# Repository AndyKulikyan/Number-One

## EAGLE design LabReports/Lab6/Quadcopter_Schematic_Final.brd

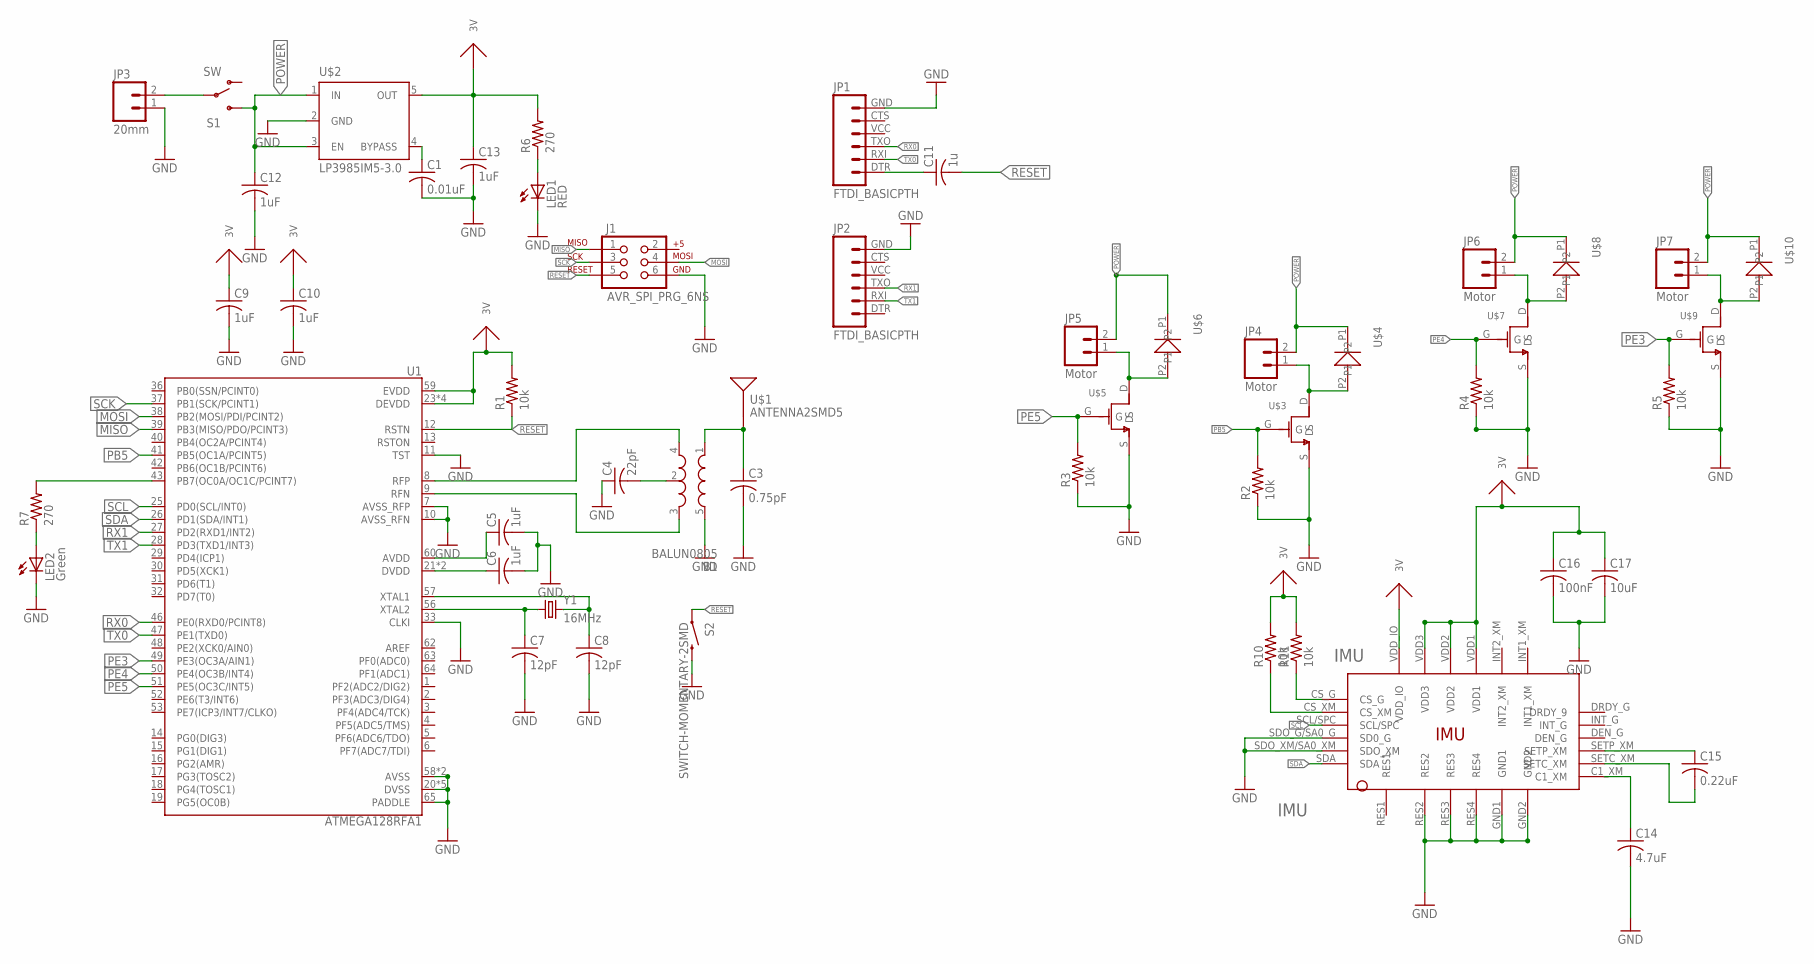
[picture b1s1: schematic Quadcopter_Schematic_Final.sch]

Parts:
B1: BALUN0805; BALUN
C1: 0.01uF; C0805
C3: 0.75pF; C0805
C4: 22pF; C0805
C5, C6, C9, C10, C12, C13: 1uF; C0805
C7, C8: 12pF; C0805
C11: 1u; C0805
C14: 4.7uF; C0805
C15: 0.22uF; C0805
C16: 100nF; C0805
C17: 10uF; C0805
IMU: IMU; LSM9DS0
J1: AVR_SPI_PRG_6NS; 2X3-NS
JP1, JP2: FTDI_BASICPTH; FTDI_BASIC
JP3: 20mm; 1X02
JP4, JP5, JP6, JP7: Motor; 1X02
LED1: RED; CHIP-LED0805
LED2: Green; CHIP-LED0805
R1, R2, R3, R4, R5, R10, R11: 10k; R0805
R6, R7: 270; R0805
S1: SW; SWITCH-SPDT
S2: SWITCH-MOMENTARY-2SMD; TACTILE_SWITCH_SMD
U1: ATMEGA128RFA1; QFN-64
U$1: ANTENNA2SMD5; ANTENNA-CHIP5
U$2: LP3985IM5-3.0; SOT23-DBV
U$3, U$5, U$7, U$9: NMOS; SI2302DS_MOSFET
U$4, U$6, U$8, U$10: Diode; BAS16WS_DIODE
Y1: 16MHz; CRYSTAL-SMD-5X3

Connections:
3V: C9.1, C10.1, C13.1, C16.1, C17.1, IMU.VDD1, IMU.VDD2, IMU.VDD3, IMU.VDD_IO, R1.2, R6.2, R10.2, R11.2, U1.23 (DEVDD), U1.34 (DEVDD), U1.44 (DEVDD), U1.54 (DEVDD), U1.59 (EVDD), U$2.5 (OUT)
FTDI: C11.1, JP1.DTR (1)
GND: B1.5 (GND), C1.2, C3.2, C4.1, C5.2, C6.2, C7.2, C8.2, C9.2, C10.2, C12.2, C13.2, C14.2, C16.2, C17.2, IMU.GND1, IMU.GND2, IMU.RES2, IMU.RES3, IMU.RES4, IMU.SDO_G/SA0_G (SD0_G), IMU.SDO_XM/SA0_XM (SDO_XM), J1.6, JP1.GND (6), JP2.GND (6), JP3.1, LED1.C, LED2.C, R2.1, R3.1, R4.1, R5.1, S2.3 (2), U1.7 (AVSS_RFP), U1.10 (AVSS_RFN), U1.11 (TST), U1.20 (DVSS), U1.24 (DVSS), U1.33 (CLKI), U1.35 (DVSS), U1.45 (DVSS), U1.55 (DVSS), U1.58 (AVSS), U1.61 (AVSS), U1.65 (PADDLE), U$2.2 (GND), U$3.S, U$5.S, U$7.S, U$9.S
MISO: J1.1, U1.39 (PB3(MISO/PDO/PCINT3))
MOSI: J1.4, U1.38 (PB2(MOSI/PDI/PCINT2))
unnamed: B1.4 (OUT1), U1.8 (RFP)
unnamed: JP5.1, U$5.D, U$6.P2
unnamed: JP3.2, S1.2
unnamed: C5.1, U1.60 (AVDD)
unnamed: C6.1, U1.21 (DVDD), U1.22 (DVDD)
unnamed: B1.2 (GND), C4.2
unnamed: B1.3 (OUT2), U1.9 (RFN)
unnamed: C8.1, U1.57 (XTAL1), Y1.3 (2)
unnamed: B1.1 (IN), C3.1, U$1.FEED
unnamed: LED1.A, R6.1
unnamed: LED2.A, R7.1
unnamed: C7.1, U1.56 (XTAL2), Y1.1
unnamed: C1.1, U$2.4 (BYPASS)
unnamed: IMU.CS_G, R11.1
unnamed: IMU.CS_XM, R10.1
unnamed: JP4.1, U$3.D, U$4.P2
unnamed: C14.1, IMU.C1_XM
unnamed: C15.2, IMU.SETC_XM
unnamed: C15.1, IMU.SETP_XM
unnamed: JP6.1, U$7.D, U$8.P2
unnamed: JP7.1, U$9.D, U$10.P2
PB5: R2.2, U1.41 (PB5(OC1A/PCINT5)), U$3.G
PB7: R7.2, U1.43 (PB7(OC0A/OC1C/PCINT7))
PE3: R5.2, U1.49 (PE3(OC3A/AIN1)), U$9.G
PE4: R4.2, U1.50 (PE4(OC3B/INT4)), U$7.G
PE5: R3.2, U1.51 (PE5(OC3C/INT5)), U$5.G
POWER: C12.1, JP4.2, JP5.2, JP6.2, JP7.2, S1.3 (S), U$2.1 (IN), U$2.3 (EN), U$4.P1, U$6.P1, U$8.P1, U$10.P1
RESET: C11.2, J1.5, R1.1, S2.1, U1.12 (RSTN)
RX0: JP1.TXO (3), U1.46 (PE0(RXD0/PCINT8))
RX1: JP2.TXO (3), U1.27 (PD2(RXD1/INT2))
SCK: J1.3, U1.37 (PB1(SCK/PCINT1))
SCL: IMU.SCL/SPC, U1.25 (PD0(SCL/INT0))
SDA: IMU.SDA, U1.26 (PD1(SDA/INT1))
TX0: JP1.RXI (2), U1.47 (PE1(TXD0))
TX1: JP2.RXI (2), U1.28 (PD3(TXD1/INT3))

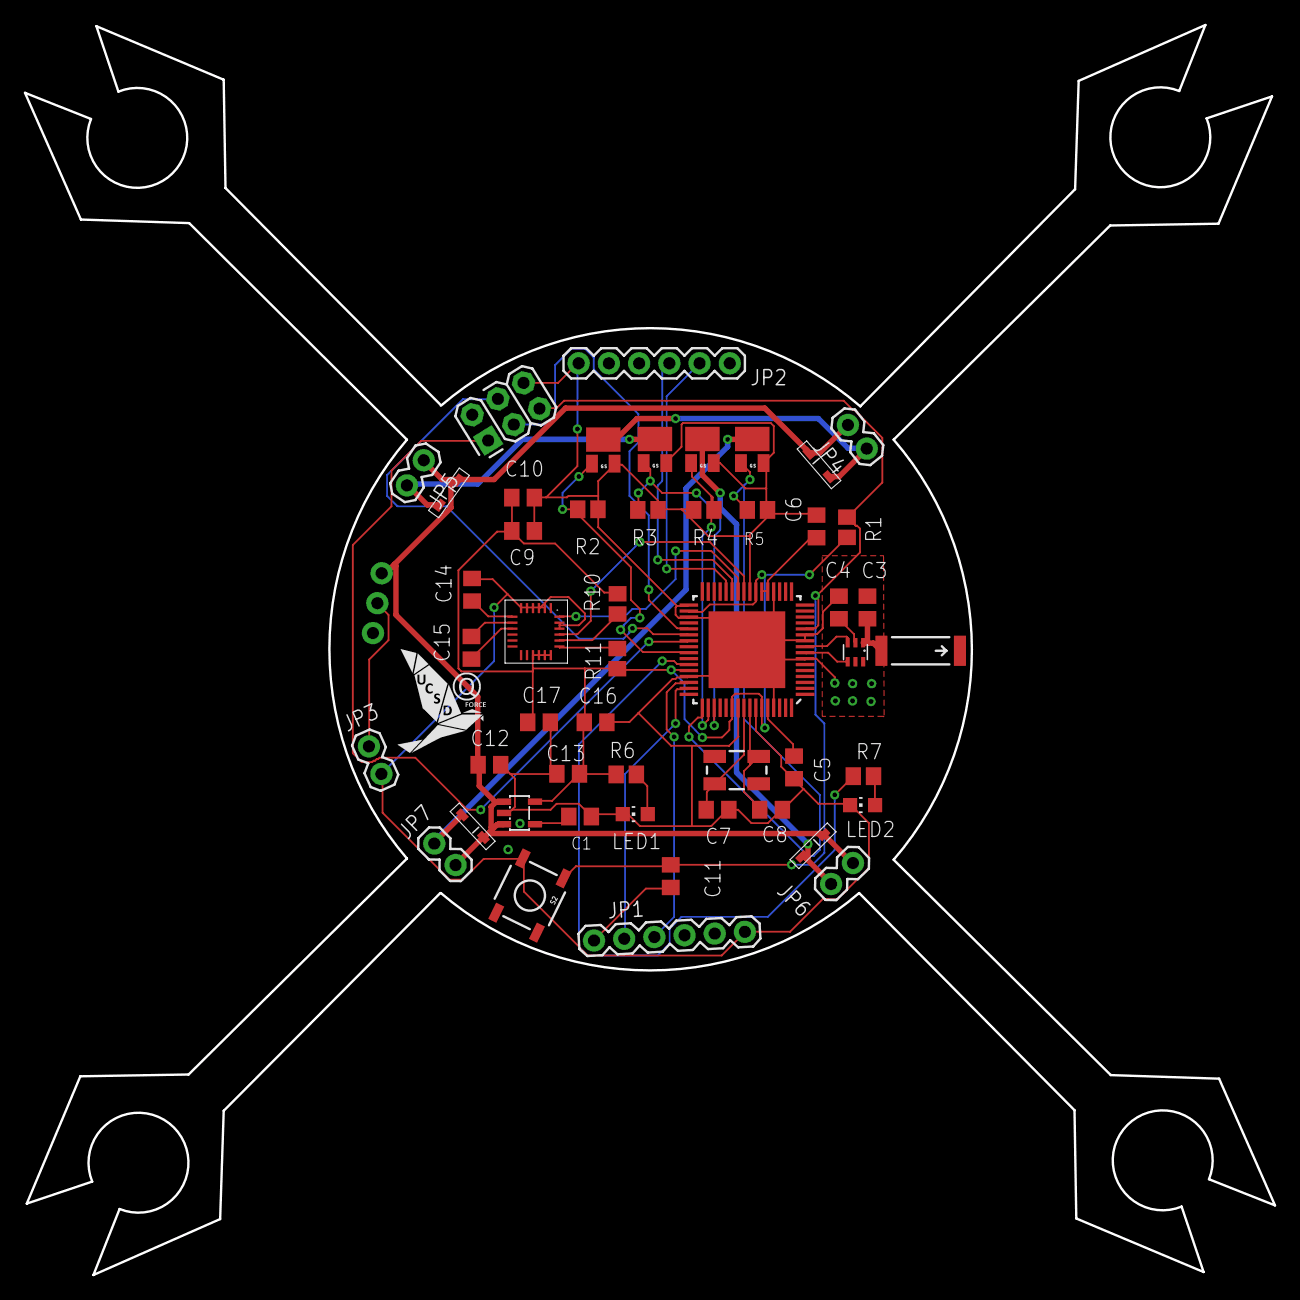
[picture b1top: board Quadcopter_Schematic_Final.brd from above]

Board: 2 copper layers, 105.0 x 105.1 mm, 53 parts (0 on the bottom side), 40 nets.

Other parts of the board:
U$11: LOGOSBOTTOM
U$12: LOGOS

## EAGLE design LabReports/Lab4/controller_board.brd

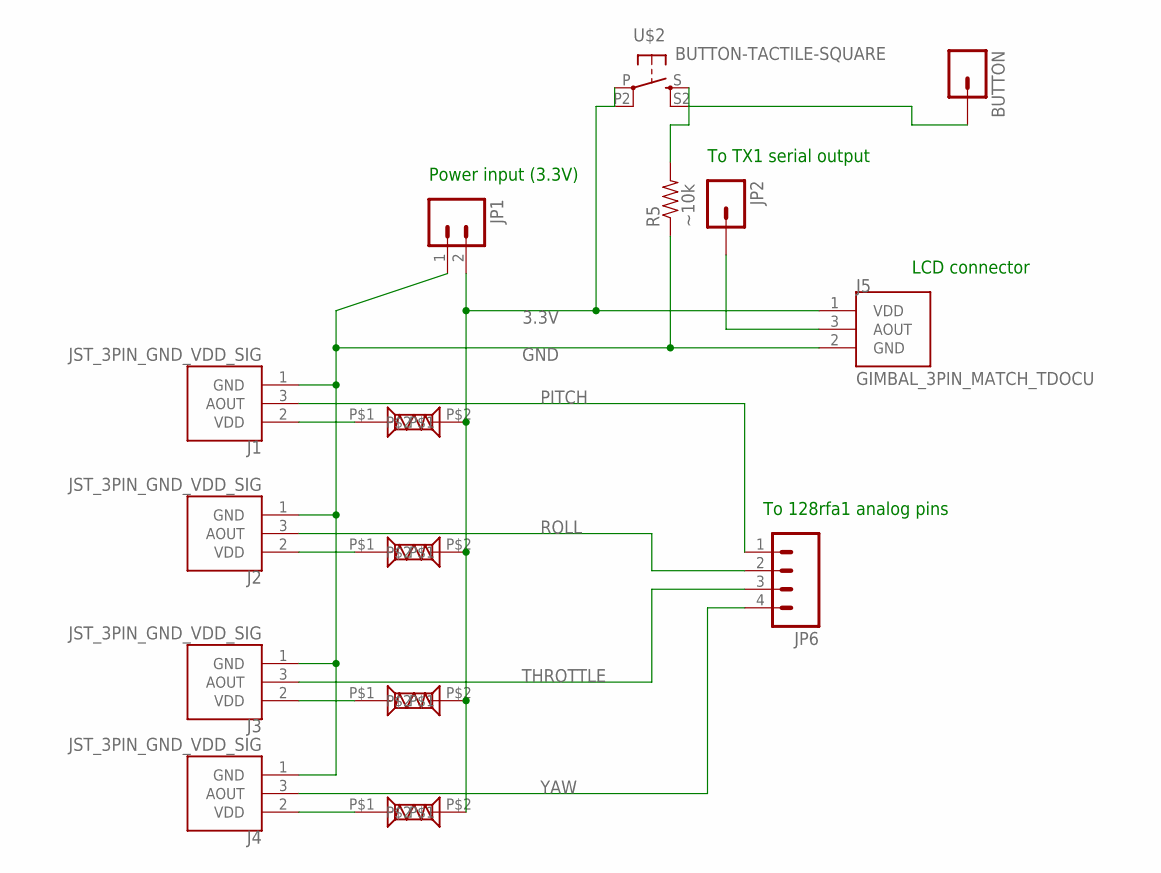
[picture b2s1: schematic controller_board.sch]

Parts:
BUTTON: M01PTH; 1X01
J1, J2, J3, J4: JST_3PIN_GND_VDD_SIG; JST-3-PTH-REVERSE
J5: GIMBAL_3PIN_MATCH_TDOCU; JST-3-PTH
JP1: M021X02_NO_SILK; 1X02_NO_SILK
JP2: M01PTH; 1X01
JP6: M04PTH; 1X04
R, R3: 4k; CRF12_RESISTOR
R2, R4: 2k; CRF12_RESISTOR
R5: ~10k; AXIAL-0.4
U$2: BUTTON-TACTILE-SQUARE; BUTTON-TACTILE-SQUARE-ADAFRUIT1010

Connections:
3.3V: J5.1 (VDD), JP1.2, R.P$2, R2.P$2, R3.P$2, R4.P$2, U$2.P, U$2.P2 (P1)
GND: J1.1 (GND), J2.1 (GND), J3.1 (GND), J4.1 (GND), J5.2 (GND), JP1.1, R5.P$1 (1)
unnamed: J1.2 (VDD), R.P$1
unnamed: J2.2 (VDD), R2.P$1
unnamed: J4.2 (VDD), R4.P$1
unnamed: J3.2 (VDD), R3.P$1
unnamed: BUTTON.1, R5.P$2 (2), U$2.S, U$2.S2 (S1)
unnamed: J5.3 (AOUT), JP2.1
PITCH: J1.3 (AOUT), JP6.1
ROLL: J2.3 (AOUT), JP6.2
THROTTLE: J3.3 (AOUT), JP6.3
YAW: J4.3 (AOUT), JP6.4

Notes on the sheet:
To 128rfa1 analog pins
LCD connector
Power input (3.3V)
To TX1 serial output

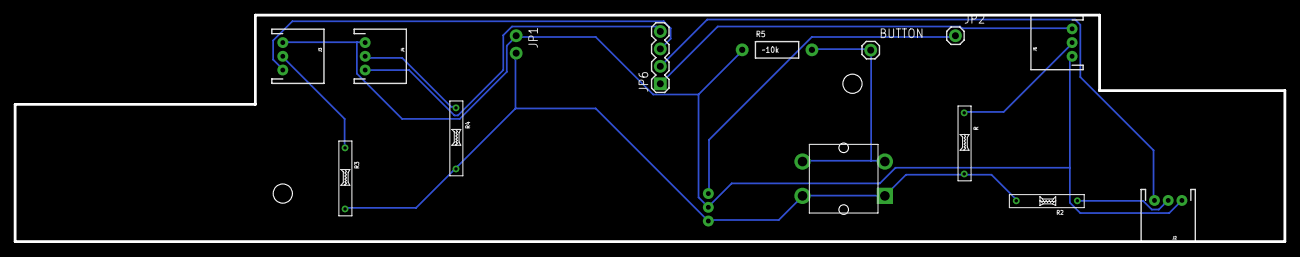
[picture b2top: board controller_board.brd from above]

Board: 2 copper layers, 185.0 x 33.0 mm, 16 parts (1 on the bottom side), 12 nets.

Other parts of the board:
U$1: CONNECTOR_BOARD_OUTLINE

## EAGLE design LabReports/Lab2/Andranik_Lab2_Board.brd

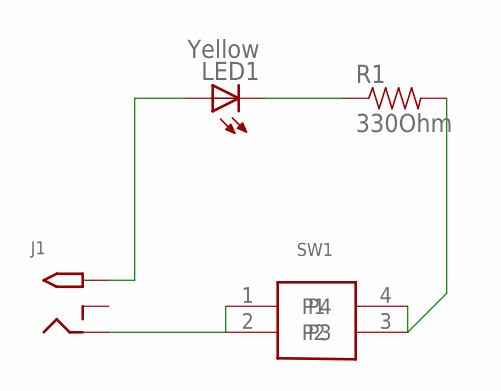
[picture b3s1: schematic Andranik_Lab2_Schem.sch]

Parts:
J1: 2.1MMJACKTHM; PJ-102A
LED1: Yellow; LED5MM
R1: 330Ohm; AXIAL-0.3
SW1: BUTTON-TACTILE-SQUARE

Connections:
unnamed: J1.TIP, LED1.A
unnamed: LED1.K (C), R1.P$1 (1)
unnamed: R1.P$2 (2), SW1.3, SW1.4
unnamed: J1.RING, SW1.1, SW1.2

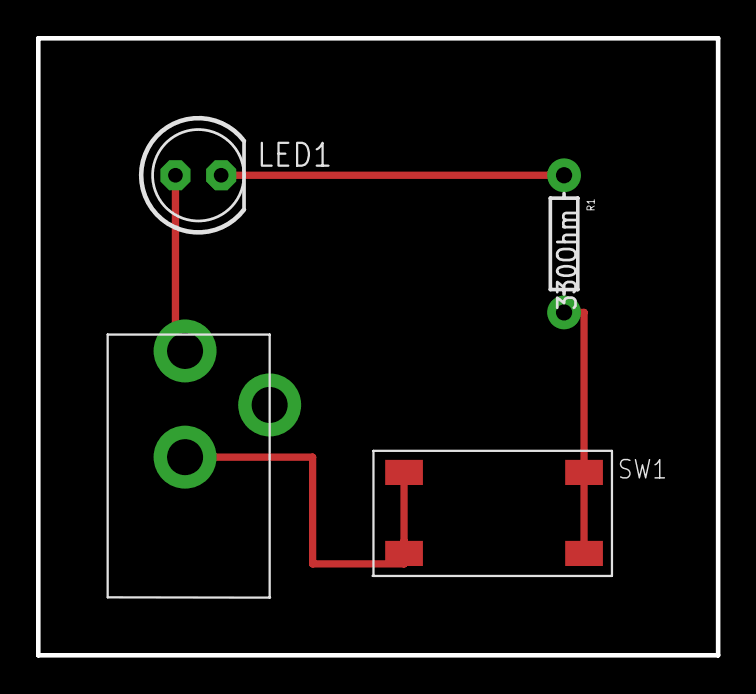
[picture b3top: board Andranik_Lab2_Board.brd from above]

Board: 2 copper layers, 37.8 x 34.3 mm, 4 parts (0 on the bottom side), 4 nets.

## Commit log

2015-04-10 Lab 2 Report Turn in
2015-04-15 Lab 3 Report
2015-04-17 Lab Report #4: Building Circuit Parts
2015-04-24 Quadcopter Schematic for Lab #5
2015-05-05 Review of Daniel Knapp's Team's Schematic
2015-05-06 Lab 6 Board Routing
2015-05-12 Final Layout of the Board
2015-05-12 board layout
2015-05-17 BOM.CSV File

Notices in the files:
parts and their libraries:
SparkFun-Connectors: Licensing: Creative Commons ShareAlike 4.0 International - https://creativecommons.org/licenses/by-sa/4.0
